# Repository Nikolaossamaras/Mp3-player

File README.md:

# Mp3-player
>this reposetory includes the BOM file ,the step files, the pcb files and the firmware for my first ever mp3-player

## Why i made it
This past month i don't have really good internet at home but i still want to listen to music so that a reason why i build this project. Another reason was that i don't want to listening to those annoying ads of spotify nor pay for the premiumm. Having an mp3 player as an accessory also drawed my attention and having a custom one seemed a ton more cool

## does it have something special
To be honest it does not have any new/special function , but the thing that makes it special for me is that i made it myself and that i will now have an accessory that is cool and functionable.

## Step files
you can download the step files from the CAD folder

## Firmware
to import the firmare to the board just plug the type c usb connector to the plug and while pressing the boot button upload the code from arduino.ide to the wroom. After the upload restart the pcb.

## PCB
download the pcb kicad files from the PCB folder

## Licence
this project is under the MIT licence

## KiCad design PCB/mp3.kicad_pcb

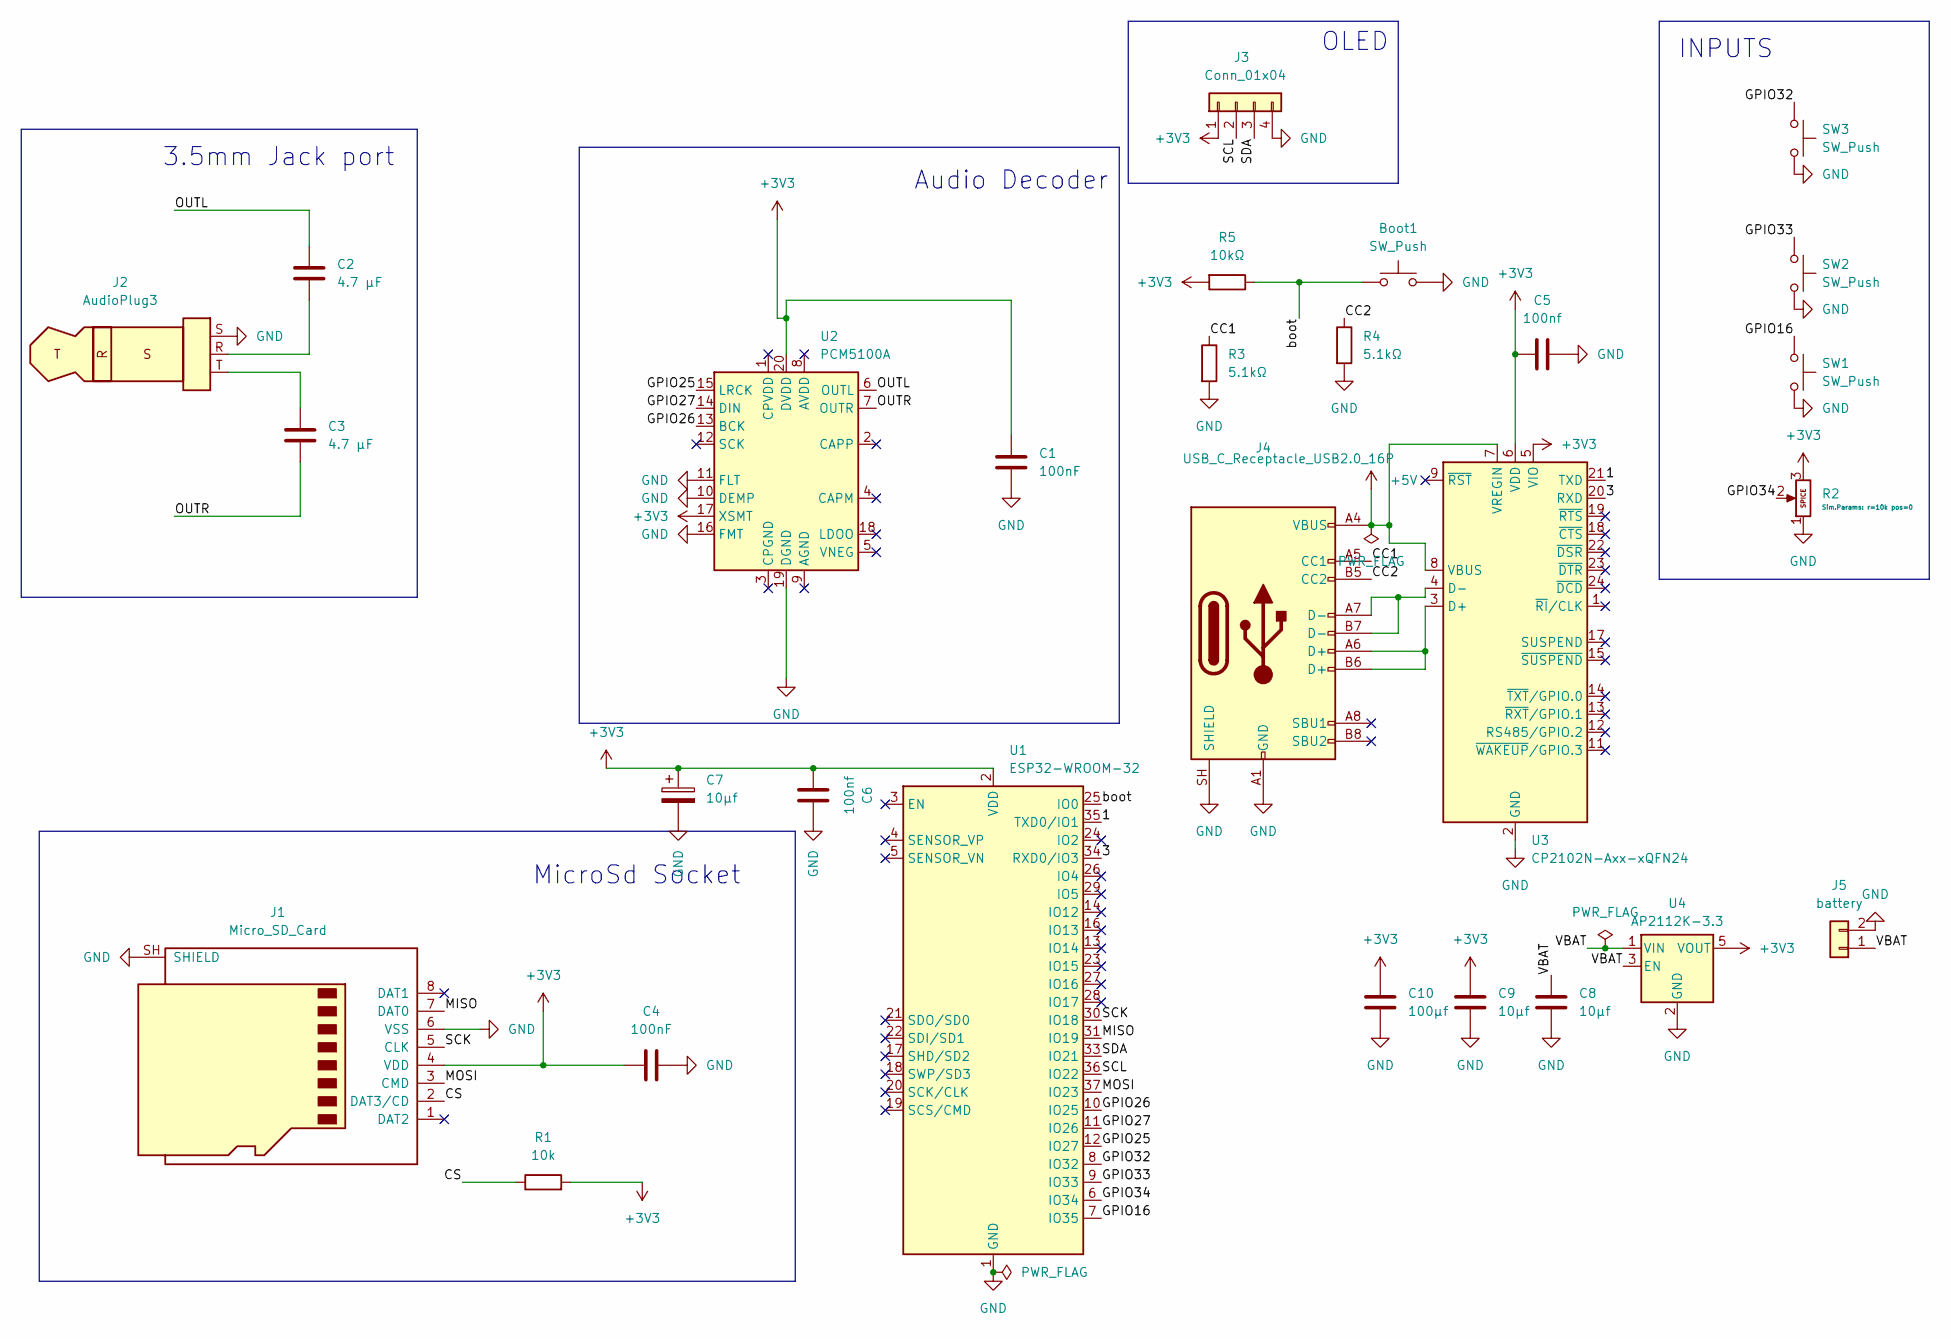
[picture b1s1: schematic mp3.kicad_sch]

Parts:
Boot1: SW_Push; SW_PUSH_6mm
C1, C4: 100nF; C_Disc_D5.0mm_W2.5mm_P5.00mm
C2, C3: 4.7 µF; CP_Radial_D5.0mm_P2.00mm
C5, C6: 100nf; C_Disc_D5.0mm_W2.5mm_P5.00mm
C7: 10μf; CP_Radial_D5.0mm_P2.00mm
C8, C9: 10μf; C_0805_2012Metric
C10: 100μf; CP_Elec_6.3x5.4
J1: Micro_SD_Card; microSD_HC_Molex_104031-0811
J2: AudioPlug3; Jack_3.5mm_CUI_SJ1-3533NG_Horizontal
J3: Conn_01x04; PinSocket_1x04_P2.54mm_Vertical
J4: USB_C_Receptacle_USB2.0_16P; USB_C_Receptacle_GCT_USB4105-xx-A_16P_TopMnt_Horizontal
J5: battery; Molex_KK-254_AE-6410-02A_1x02_P2.54mm_Vertical
R1: 10k; R_Axial_DIN0207_L6.3mm_D2.5mm_P10.16mm_Horizontal
R2: Potentiometer; Potentiometer_Alps_RK09K_Single_Vertical
R3, R4: 5.1kΩ; R_Axial_DIN0207_L6.3mm_D2.5mm_P10.16mm_Horizontal
R5: 10kΩ; R_Axial_DIN0207_L6.3mm_D2.5mm_P10.16mm_Horizontal
SW1, SW2, SW3: SW_Push; SW_PUSH_6mm
U1: ESP32-WROOM-32
U2: PCM5100A; TSSOP-20_4.4x6.5mm_P0.65mm
U3: CP2102N-Axx-xQFN24; QFN-24-1EP_4x4mm_P0.5mm_EP2.6x2.6mm
U4: AP2112K-3.3; SOT-23-5

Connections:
+3V3: C1.1, C4.1, C5.1, C6.1, C7.1, C9.1, C10.1, J1.4 (VDD), J3.1, R1.2, R2.3, R5.2, U1.2 (VDD), U2.17 (XSMT), U2.20 (DVDD), U3.5 (VIO), U3.6 (VDD), U4.5 (VOUT)
+5V: J4.A4 (VBUS), J4.A9 (VBUS), J4.B4 (VBUS), J4.B9 (VBUS), U3.7 (VREGIN), U3.8 (VBUS)
/1: U1.35 (TXD0/IO1), U3.21 (TXD)
/3: U1.34 (RXD0/IO3), U3.20 (RXD)
/CC1: J4.A5 (CC1), R3.1
/CC2: J4.B5 (CC2), R4.1
/CS: J1.2 (DAT3/CD), R1.1
/GPIO16: SW1.1, U1.7 (IO35)
/GPIO25: U1.12 (IO27), U2.15 (LRCK)
/GPIO26: U1.10 (IO25), U2.13 (BCK)
/GPIO27: U1.11 (IO26), U2.14 (DIN)
/GPIO32: SW3.1, U1.8 (IO32)
/GPIO33: SW2.1, U1.9 (IO33)
/GPIO34: R2.2, U1.6 (IO34)
/MISO: J1.7 (DAT0), U1.31 (IO19)
/MOSI: J1.3 (CMD), U1.37 (IO23)
/OUTL: C2.1, U2.6 (OUTL)
/OUTR: C3.2, U2.7 (OUTR)
/SCK: J1.5 (CLK), U1.30 (IO18)
/SCL: J3.2, U1.36 (IO22)
/SDA: J3.3, U1.33 (IO21)
/VBAT: C8.1, J5.1, U4.1 (VIN), U4.3 (EN)
/boot: Boot1.1, R5.1, U1.25 (IO0)
GND: Boot1.2, C1.2, C4.2, C5.2, C6.2, C7.2, C8.2, C9.2, C10.2, J1.6 (VSS), J1.SH (SHIELD), J2.S, J3.4, J4.A1 (GND), J4.A12 (GND), J4.B1 (GND), J4.B12 (GND), J4.SH (SHIELD), J5.2, R2.1, R3.2, R4.2, SW1.2, SW2.2, SW3.2, U1.1 (GND), U1.15 (GND), U1.38 (GND), U1.39 (GND), U2.10 (DEMP), U2.11 (FLT), U2.16 (FMT), U2.19 (DGND), U3.2 (GND), U3.25 (GND), U4.2 (GND)
unnamed: C2.2, J2.R
unnamed: C3.1, J2.T
unnamed: J4.A6 (D+), J4.B6 (D+), U3.3 (D+)
unnamed: J4.A7 (D-), J4.B7 (D-), U3.4 (D-)

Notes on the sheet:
MicroSd Socket
3.5mm Jack port
OLED
Audio Decoder
INPUTS

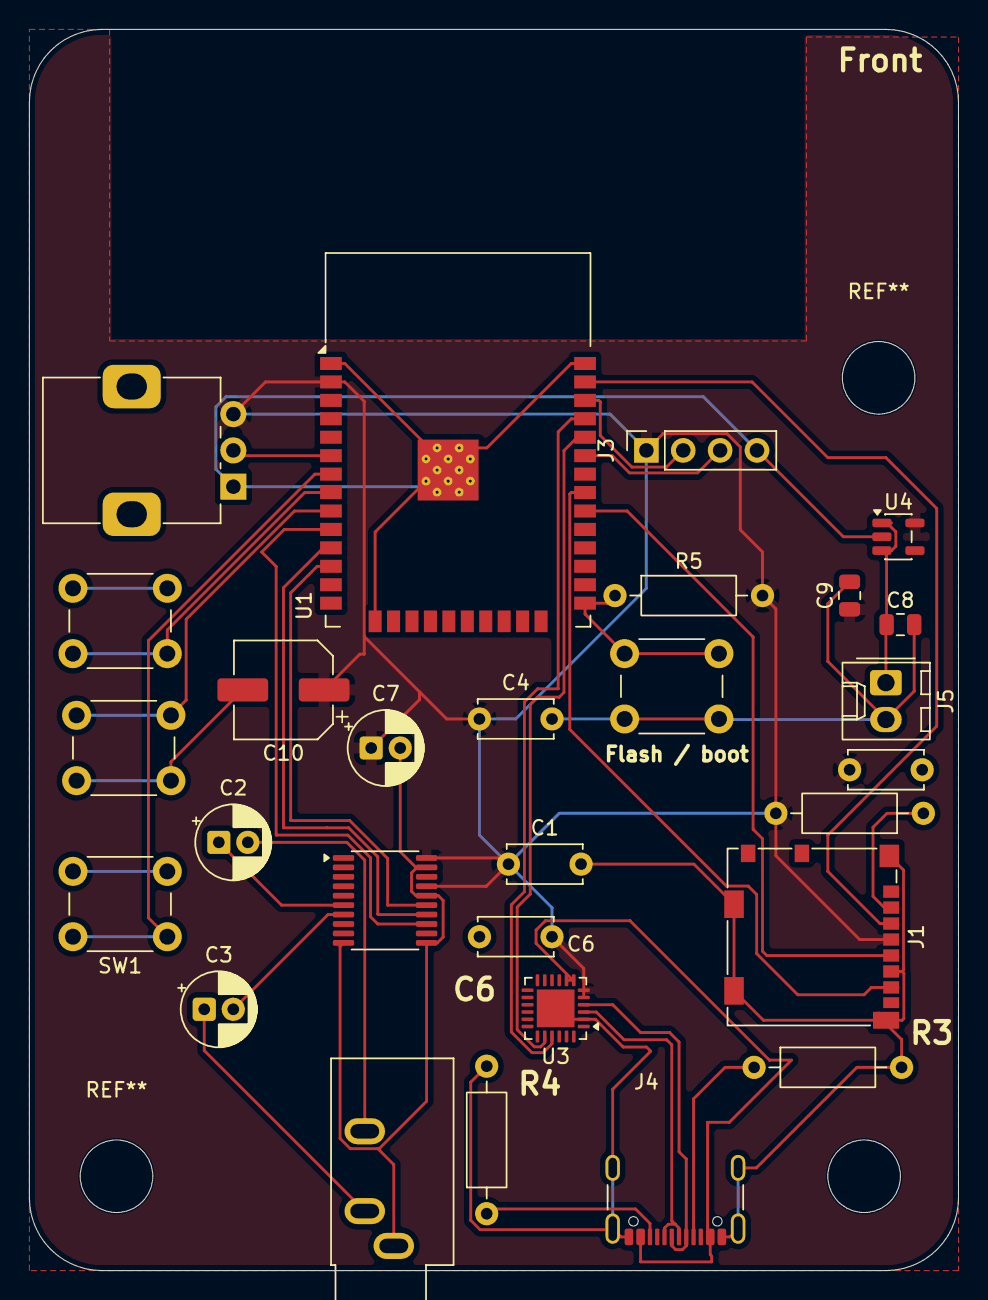
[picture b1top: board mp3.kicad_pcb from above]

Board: 2 copper layers, 64.0 x 85.5 mm, 28 parts (0 on the bottom side), 28 nets.

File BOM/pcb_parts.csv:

Reference,Qty,Value,DNP,Exclude from BOM,Exclude from Board,Footprint,Datasheet
"Boot1,SW1,SW2,SW3",4,SW_Push,,,,Button_Switch_THT:SW_PUSH_6mm,
"C1,C4",2,100nF,,,,Capacitor_THT:C_Disc_D5.0mm_W2.5mm_P5.00mm,
"C2,C3",2,4.7 µF,,,,Capacitor_THT:CP_Radial_D5.0mm_P2.00mm,
"C5,C6",2,100nf,,,,Capacitor_THT:C_Disc_D5.0mm_W2.5mm_P5.00mm,
C7,1,10μf,,,,Capacitor_THT:CP_Radial_D5.0mm_P2.00mm,
"C8,C9",2,10μf,,,,Capacitor_SMD:C_0805_2012Metric,
C10,1,100μf,,,,Capacitor_SMD:CP_Elec_6.3x5.4,
J1,1,Micro_SD_Card,,,,Connector_Card:microSD_HC_Molex_104031-0811,https://www.we-online.com/components/products/datasheet/6930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
J2,1,AudioPlug3,,,,Connector_Audio:Jack_3.5mm_CUI_SJ1-3533NG_Horizontal,
J3,1,Conn_01x04,,,,Connector_PinSocket_2.54mm:PinSocket_1x04_P2.54mm_Vertical,
J4,1,USB_C_Receptacle_USB2.0_16P,,,,Connector_USB:USB_C_Receptacle_GCT_USB4105-xx-A_16P_TopMnt_Horizontal,https://www.usb.org/sites/default/files/documents/usb_type-c.zip
J5,1,battery,,,,Connector_Molex:Molex_KK-254_AE-6410-02A_1x02_P2.54mm_Vertical,
R1,1,10k,,,,Resistor_THT:R_Axial_DIN0207_L6.3mm_D2.5mm_P10.16mm_Horizontal,
R2,1,Potentiometer,,,,Potentiometer_THT:Potentiometer_Alps_RK09K_Single_Vertical,
"R3,R4",2,5.1kΩ,,,,Resistor_THT:R_Axial_DIN0207_L6.3mm_D2.5mm_P10.16mm_Horizontal,
R5,1,10kΩ,,,,Resistor_THT:R_Axial_DIN0207_L6.3mm_D2.5mm_P10.16mm_Horizontal,
U1,1,ESP32-WROOM-32,,,,RF_Module:ESP32-WROOM-32,https://www.espressif.com/sites/default/files/documentation/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
U2,1,PCM5100A,,,,Package_SO:TSSOP-20_4.4x6.5mm_P0.65mm,https://www.ti.com/lit/ds/symlink/pcm5100a.pdf
U3,1,CP2102N-Axx-xQFN24,,,,Package_DFN_QFN:QFN-24-1EP_4x4mm_P0.5mm_EP2.6x2.6mm,https://www.silabs.com/documents/public/data-sheets/cp2102n-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
U4,1,AP2112K-3.3,,,,Package_TO_SOT_SMD:SOT-23-5,https://www.diodes.com/assets/Datasheets/AP2112.pdf
